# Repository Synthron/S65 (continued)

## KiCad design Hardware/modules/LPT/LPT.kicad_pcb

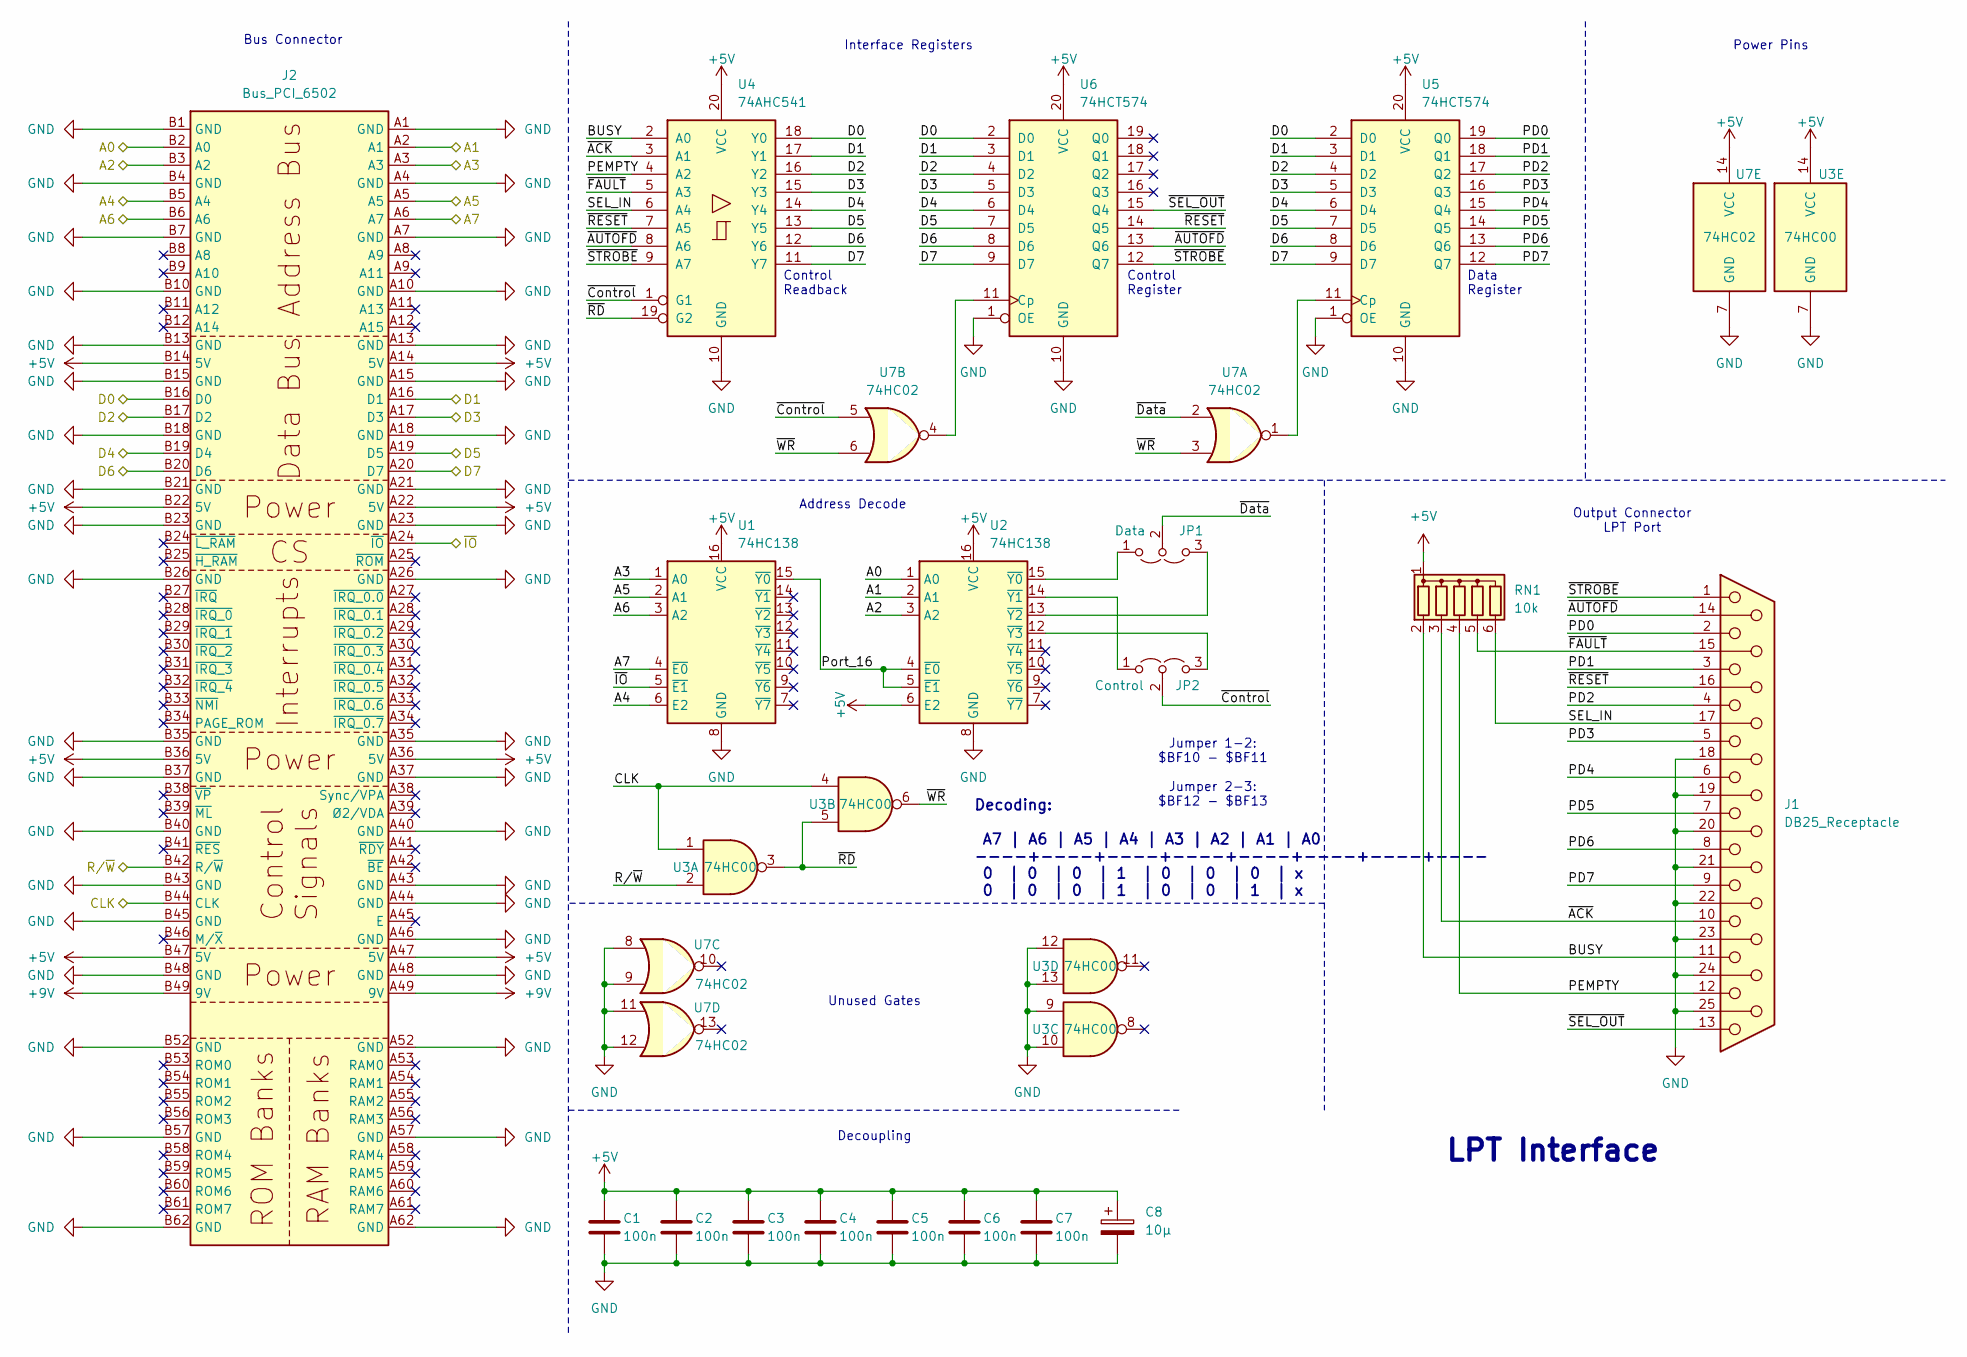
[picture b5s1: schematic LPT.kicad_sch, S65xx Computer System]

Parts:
C1, C2, C3, C4, C5, C6, C7: 100n; C_0805_2012Metric
C8: 10µ; CP_Radial_D5.0mm_P2.50mm
J1: DB25_Receptacle; DSUB-25_Female_EdgeMount_P2.77mm
J2: Bus_PCI_6502; BUS_PCI
JP1: Data; SolderJumper-3_P2.0mm_Open_TrianglePad1.0x1.5mm_NumberLabels
JP2: Control; SolderJumper-3_P2.0mm_Open_TrianglePad1.0x1.5mm_NumberLabels
RN1: 10k; R_Array_SIP6
U1, U2: 74HC138; DIP-16_W7.62mm
U3: 74HC00; DIP-14_W7.62mm
U4: 74AHC541; DIP-20_W7.62mm
U5, U6: 74HCT574; DIP-20_W7.62mm
U7: 74HC02; DIP-14_W7.62mm

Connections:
+5V: C1.1, C2.1, C3.1, C4.1, C5.1, C6.1, C7.1, C8.1, J2.A14 (5V), J2.A22 (5V), J2.A36 (5V), J2.A47 (5V), J2.B14 (5V), J2.B22 (5V), J2.B36 (5V), J2.B47 (5V), RN1.1 (common), U1.16 (VCC), U2.6 (E2), U2.16 (VCC), U3.14 (VCC), U4.20 (VCC), U5.20 (VCC), U6.20 (VCC), U7.14 (VCC)
+9V: J2.A49 (9V), J2.B49 (9V)
/A0: J2.B2 (A0), U2.1 (A0)
/A1: J2.A2 (A1), U2.2 (A1)
/A2: J2.B3 (A2), U2.3 (A2)
/A3: J2.A3, U1.1 (A0)
/A4: J2.B5 (A4), U1.6 (E2)
/A5: J2.A5, U1.2 (A1)
/A6: J2.B6 (A6), U1.3 (A2)
/A7: J2.A6 (A7), U1.4 (~E0)
/BUSY: J1.11, RN1.2 (R1), U4.2 (A0)
/CLK: J2.B44 (CLK), U3.1, U3.4
/D0: J2.B16 (D0), U4.18 (Y0), U5.2 (D0), U6.2 (D0)
/D1: J2.A16 (D1), U4.17 (Y1), U5.3 (D1), U6.3 (D1)
/D2: J2.B17 (D2), U4.16 (Y2), U5.4 (D2), U6.4 (D2)
/D3: J2.A17 (D3), U4.15 (Y3), U5.5 (D3), U6.5 (D3)
/D4: J2.B19 (D4), U4.14 (Y4), U5.6 (D4), U6.6 (D4)
/D5: J2.A19 (D5), U4.13 (Y5), U5.7 (D5), U6.7 (D5)
/D6: J2.B20 (D6), U4.12 (Y6), U5.8 (D6), U6.8 (D6)
/D7: J2.A20 (D7), U4.11 (Y7), U5.9 (D7), U6.9 (D7)
/PD0: J1.2, U5.19 (Q0)
/PD1: J1.3, U5.18 (Q1)
/PD2: J1.4, U5.17 (Q2)
/PD3: J1.5, U5.16 (Q3)
/PD4: J1.6, U5.15 (Q4)
/PD5: J1.7, U5.14 (Q5)
/PD6: J1.8, U5.13 (Q6)
/PD7: J1.9, U5.12 (Q7)
/PEMPTY: J1.12, RN1.4 (R3), U4.4 (A2)
/Port_16: U1.15 (~Y0), U2.4 (~E0), U2.5 (~E1)
/R/~W: J2.B42 (R/~W), U3.2
/SEL_IN: J1.17, RN1.6 (R5), U4.6 (A4)
/~ACK: J1.10, RN1.3 (R2), U4.3 (A1)
/~AUTOFD: J1.14, U4.8 (A6), U6.13 (Q6)
/~Control: JP2.2 (C), U4.1 (G1), U7.5
/~Data: JP1.2 (C), U7.2
/~FAULT: J1.15, RN1.5 (R4), U4.5 (A3)
/~IO: J2.A24 (~IO), U1.5 (~E1)
/~RD: U3.3, U3.5, U4.19 (G2)
/~RESET: J1.16, U4.7 (A5), U6.14 (Q5)
/~SEL_OUT: J1.13, U6.15 (Q4)
/~STROBE: J1.1, U4.9 (A7), U6.12 (Q7)
/~WR: U3.6, U7.3, U7.6
GND: C1.2, C2.2, C3.2, C4.2, C5.2, C6.2, C7.2, C8.2, J1.18, J1.19, J1.20, J1.21, J1.22, J1.23, J1.24, J1.25, J2.A1 (GND), J2.A4 (GND), J2.A7 (GND), J2.A10 (GND), J2.A13 (GND), J2.A15 (GND), J2.A18 (GND), J2.A21 (GND), J2.A23 (GND), J2.A26 (GND), J2.A35 (GND), J2.A37 (GND), J2.A40 (GND), J2.A43 (GND), J2.A44 (GND), J2.A46 (GND), J2.A48 (GND), J2.A52 (GND), J2.A57 (GND), J2.A62 (GND), J2.B1 (GND), J2.B4 (GND), J2.B7 (GND), J2.B10 (GND), J2.B13 (GND), J2.B15 (GND), J2.B18 (GND), J2.B21 (GND), J2.B23 (GND), J2.B26 (GND), J2.B35 (GND), J2.B37 (GND), J2.B40 (GND), J2.B43 (GND), J2.B45 (GND), J2.B48 (GND), J2.B52 (GND), J2.B57 (GND), J2.B62 (GND), U1.8 (GND), U2.8 (GND), U3.7 (GND), U3.9, U3.10, U3.12, U3.13, U4.10 (GND), U5.1 (OE), U5.10 (GND), U6.1 (OE), U6.10 (GND), U7.7 (GND), U7.8, U7.9, U7.11, U7.12
unnamed: JP1.1 (A), U2.15 (~Y0)
unnamed: JP1.3 (B), U2.13 (~Y2)
unnamed: JP2.1 (A), U2.14 (~Y1)
unnamed: JP2.3 (B), U2.12 (~Y3)
unnamed: U5.11 (Cp), U7.1
unnamed: U6.11 (Cp), U7.4

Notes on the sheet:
Interface Registers
Decoupling
Jumper 1-2: $BF10 - $BF11 Jumper 2-3: $BF12 - $BF13
Output Connector LPT Port
Decoding: A7 | A6 | A5 | A4 | A3 | A2 | A1 | A0 ----+----+----+----+----+----+----+---- 0 | 0 | 0 | 1 | 0 | 0 | 0 | x 0 | 0 | 0 | 1 | 0 | 0 | 1 | x
Power Pins
Address Decode
Control Register
Bus Connector
Unused Gates
Control Readback
Data Register
LPT Interface

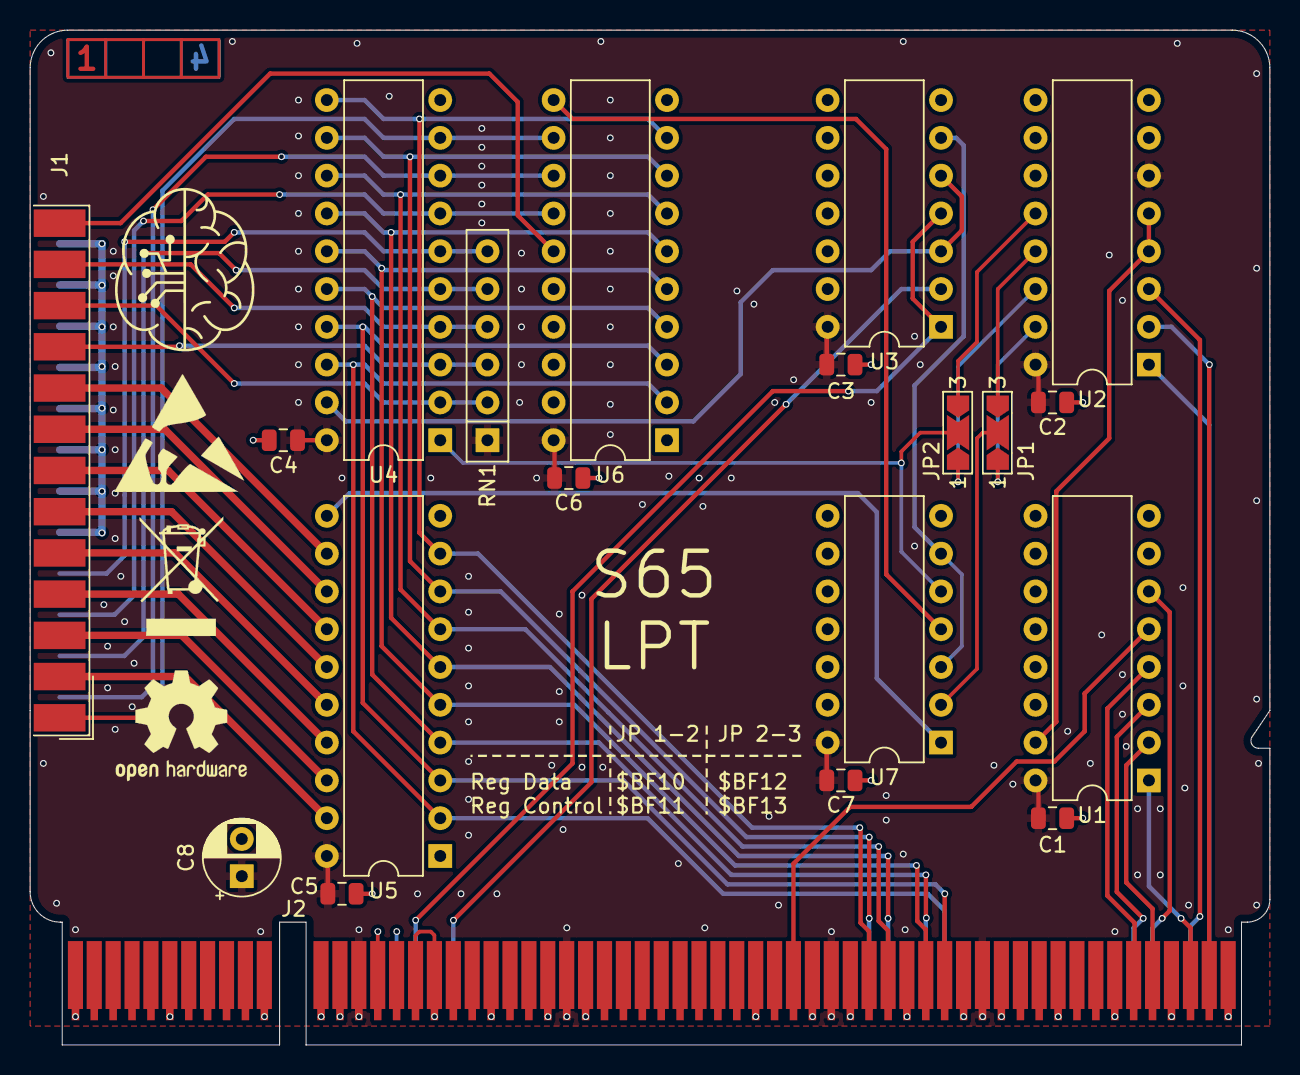
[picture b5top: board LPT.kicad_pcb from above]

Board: 4 copper layers, 83.3 x 68.2 mm, 21 parts (1 on the bottom side), 50 nets.

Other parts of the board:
Ref**: Val**; ladder_4

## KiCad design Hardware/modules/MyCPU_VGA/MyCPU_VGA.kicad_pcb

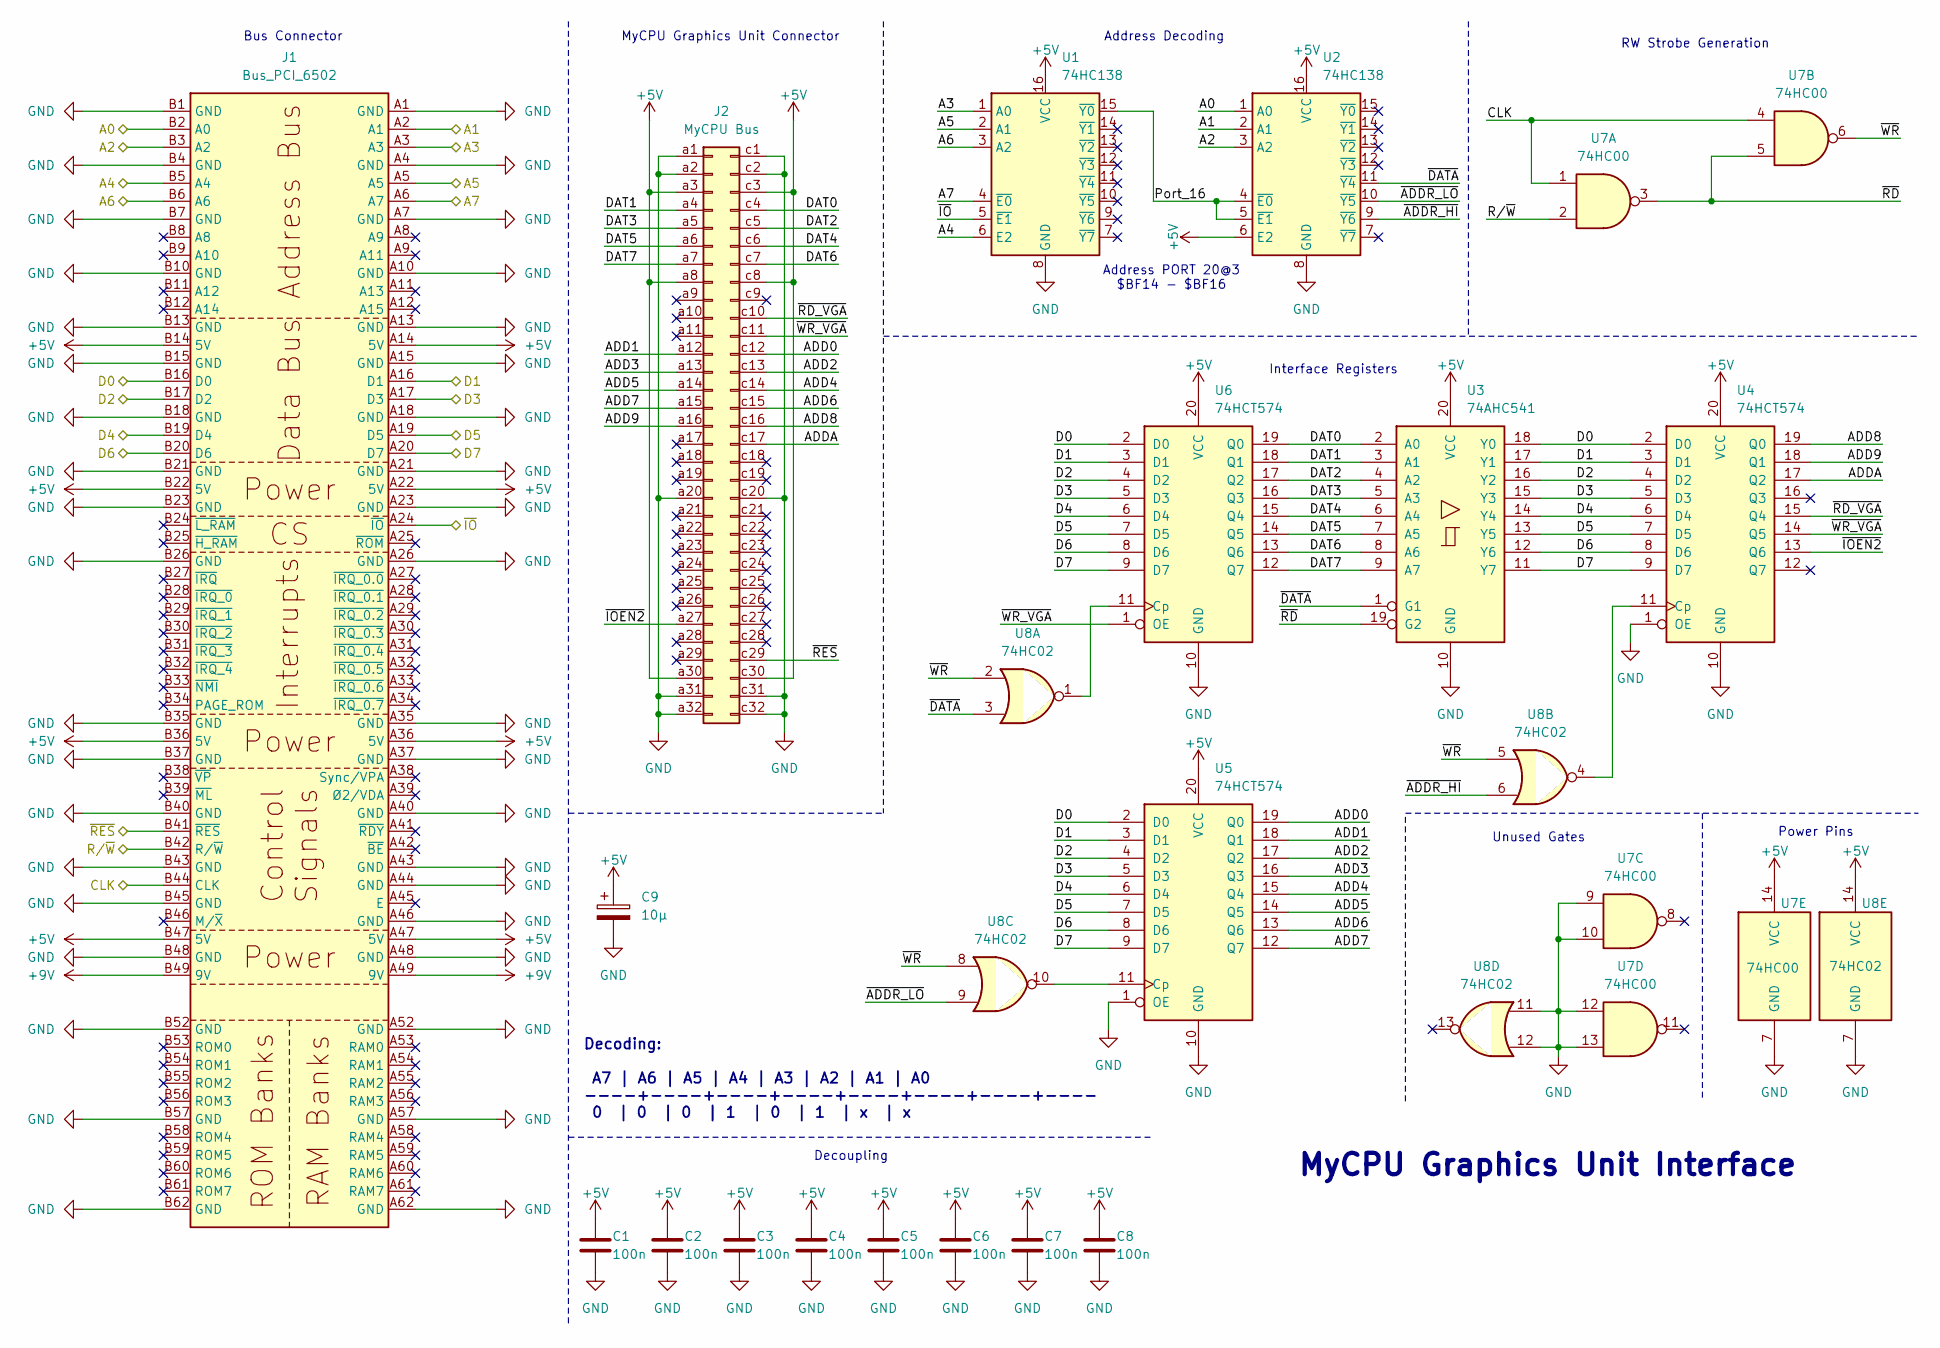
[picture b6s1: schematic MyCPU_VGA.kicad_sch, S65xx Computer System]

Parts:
C1, C2, C3, C4, C5, C6, C7, C8: 100n; C_0805_2012Metric
C9: 10µ; CP_Radial_D5.0mm_P2.50mm
J1: Bus_PCI_6502; BUS_PCI
J2: MyCPU Bus; DIN41612_C_2x32_Male_Horizontal_THT
U1, U2: 74HC138; DIP-16_W7.62mm
U3: 74AHC541; DIP-20_W7.62mm
U4, U5, U6: 74HCT574; DIP-20_W7.62mm
U7: 74HC00; DIP-14_W7.62mm
U8: 74HC02; DIP-14_W7.62mm

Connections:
+5V: C1.1, C2.1, C3.1, C4.1, C5.1, C6.1, C7.1, C8.1, C9.1, J1.A14 (5V), J1.A22 (5V), J1.A36 (5V), J1.A47 (5V), J1.B14 (5V), J1.B22 (5V), J1.B36 (5V), J1.B47 (5V), J2.a3, J2.a8, J2.a30, J2.c3, J2.c8, J2.c30, U1.16 (VCC), U2.6 (E2), U2.16 (VCC), U3.20 (VCC), U4.20 (VCC), U5.20 (VCC), U6.20 (VCC), U7.14 (VCC), U8.14 (VCC)
+9V: J1.A49 (9V), J1.B49 (9V)
/A0: J1.B2 (A0), U2.1 (A0)
/A1: J1.A2 (A1), U2.2 (A1)
/A2: J1.B3 (A2), U2.3 (A2)
/A3: J1.A3, U1.1 (A0)
/A4: J1.B5 (A4), U1.6 (E2)
/A5: J1.A5, U1.2 (A1)
/A6: J1.B6 (A6), U1.3 (A2)
/A7: J1.A6 (A7), U1.4 (~E0)
/ADD0: J2.c12, U5.19 (Q0)
/ADD1: J2.a12, U5.18 (Q1)
/ADD2: J2.c13, U5.17 (Q2)
/ADD3: J2.a13, U5.16 (Q3)
/ADD4: J2.c14, U5.15 (Q4)
/ADD5: J2.a14, U5.14 (Q5)
/ADD6: J2.c15, U5.13 (Q6)
/ADD7: J2.a15, U5.12 (Q7)
/ADD8: J2.c16, U4.19 (Q0)
/ADD9: J2.a16, U4.18 (Q1)
/ADDA: J2.c17, U4.17 (Q2)
/CLK: J1.B44 (CLK), U7.1, U7.4
/D0: J1.B16 (D0), U3.18 (Y0), U4.2 (D0), U5.2 (D0), U6.2 (D0)
/D1: J1.A16 (D1), U3.17 (Y1), U4.3 (D1), U5.3 (D1), U6.3 (D1)
/D2: J1.B17 (D2), U3.16 (Y2), U4.4 (D2), U5.4 (D2), U6.4 (D2)
/D3: J1.A17 (D3), U3.15 (Y3), U4.5 (D3), U5.5 (D3), U6.5 (D3)
/D4: J1.B19 (D4), U3.14 (Y4), U4.6 (D4), U5.6 (D4), U6.6 (D4)
/D5: J1.A19 (D5), U3.13 (Y5), U4.7 (D5), U5.7 (D5), U6.7 (D5)
/D6: J1.B20 (D6), U3.12 (Y6), U4.8 (D6), U5.8 (D6), U6.8 (D6)
/D7: J1.A20 (D7), U3.11 (Y7), U4.9 (D7), U5.9 (D7), U6.9 (D7)
/DAT0: J2.c4, U3.2 (A0), U6.19 (Q0)
/DAT1: J2.a4, U3.3 (A1), U6.18 (Q1)
/DAT2: J2.c5, U3.4 (A2), U6.17 (Q2)
/DAT3: J2.a5, U3.5 (A3), U6.16 (Q3)
/DAT4: J2.c6, U3.6 (A4), U6.15 (Q4)
/DAT5: J2.a6, U3.7 (A5), U6.14 (Q5)
/DAT6: J2.c7, U3.8 (A6), U6.13 (Q6)
/DAT7: J2.a7, U3.9 (A7), U6.12 (Q7)
/Port_16: U1.15 (~Y0), U2.4 (~E0), U2.5 (~E1)
/R/~W: J1.B42 (R/~W), U7.2
/~ADDR_HI: U2.9 (~Y6), U8.6
/~ADDR_LO: U2.10 (~Y5), U8.9
/~DATA: U2.11 (~Y4), U3.1 (G1), U8.3
/~IOEN2: J2.a27, U4.13 (Q6)
/~IO: J1.A24 (~IO), U1.5 (~E1)
/~RD_VGA: J2.c10, U4.15 (Q4)
/~RD: U3.19 (G2), U7.3, U7.5
/~RES: J1.B41 (~RES), J2.c29
/~WR_VGA: J2.c11, U4.14 (Q5), U6.1 (OE)
/~WR: U7.6, U8.2, U8.5, U8.8
GND: C1.2, C2.2, C3.2, C4.2, C5.2, C6.2, C7.2, C8.2, C9.2, J1.A1 (GND), J1.A4 (GND), J1.A7 (GND), J1.A10 (GND), J1.A13 (GND), J1.A15 (GND), J1.A18 (GND), J1.A21 (GND), J1.A23 (GND), J1.A26 (GND), J1.A35 (GND), J1.A37 (GND), J1.A40 (GND), J1.A43 (GND), J1.A44 (GND), J1.A46 (GND), J1.A48 (GND), J1.A52 (GND), J1.A57 (GND), J1.A62 (GND), J1.B1 (GND), J1.B4 (GND), J1.B7 (GND), J1.B10 (GND), J1.B13 (GND), J1.B15 (GND), J1.B18 (GND), J1.B21 (GND), J1.B23 (GND), J1.B26 (GND), J1.B35 (GND), J1.B37 (GND), J1.B40 (GND), J1.B43 (GND), J1.B45 (GND), J1.B48 (GND), J1.B52 (GND), J1.B57 (GND), J1.B62 (GND), J2.a1, J2.a2, J2.a20, J2.a31, J2.a32, J2.c1, J2.c2, J2.c20, J2.c31, J2.c32, U1.8 (GND), U2.8 (GND), U3.10 (GND), U4.1 (OE), U4.10 (GND), U5.1 (OE), U5.10 (GND), U6.10 (GND), U7.7 (GND), U7.9, U7.10, U7.12, U7.13, U8.7 (GND), U8.11, U8.12
unnamed: U4.11 (Cp), U8.4
unnamed: U5.11 (Cp), U8.10
unnamed: U6.11 (Cp), U8.1

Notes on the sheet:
Power Pins
MyCPU Graphics Unit Connector
RW Strobe Generation
Address Decoding
MyCPU Graphics Unit Interface
Interface Registers
Bus Connector
Unused Gates
Decoding: A7 | A6 | A5 | A4 | A3 | A2 | A1 | A0 ----+----+----+----+----+----+----+---- 0 | 0 | 0 | 1 | 0 | 1 | x | x
Address PORT 20@3 $BF14 - $BF16
Decoupling

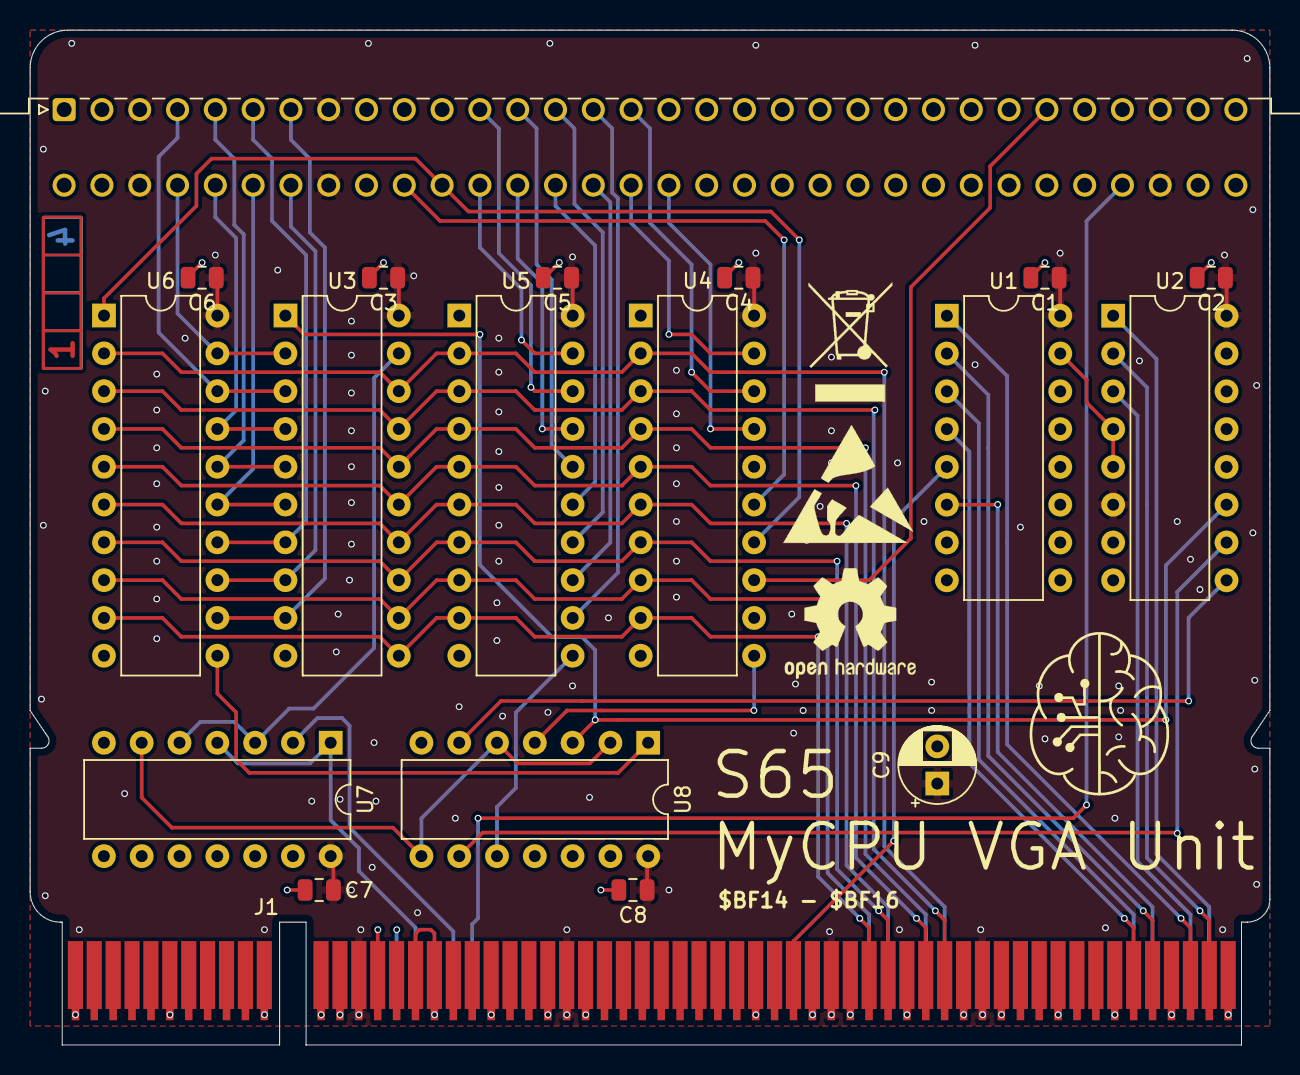
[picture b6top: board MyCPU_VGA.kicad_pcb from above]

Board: 4 copper layers, 83.3 x 68.2 mm, 20 parts (1 on the bottom side), 54 nets.

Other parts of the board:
Ref**: Val**; ladder_4

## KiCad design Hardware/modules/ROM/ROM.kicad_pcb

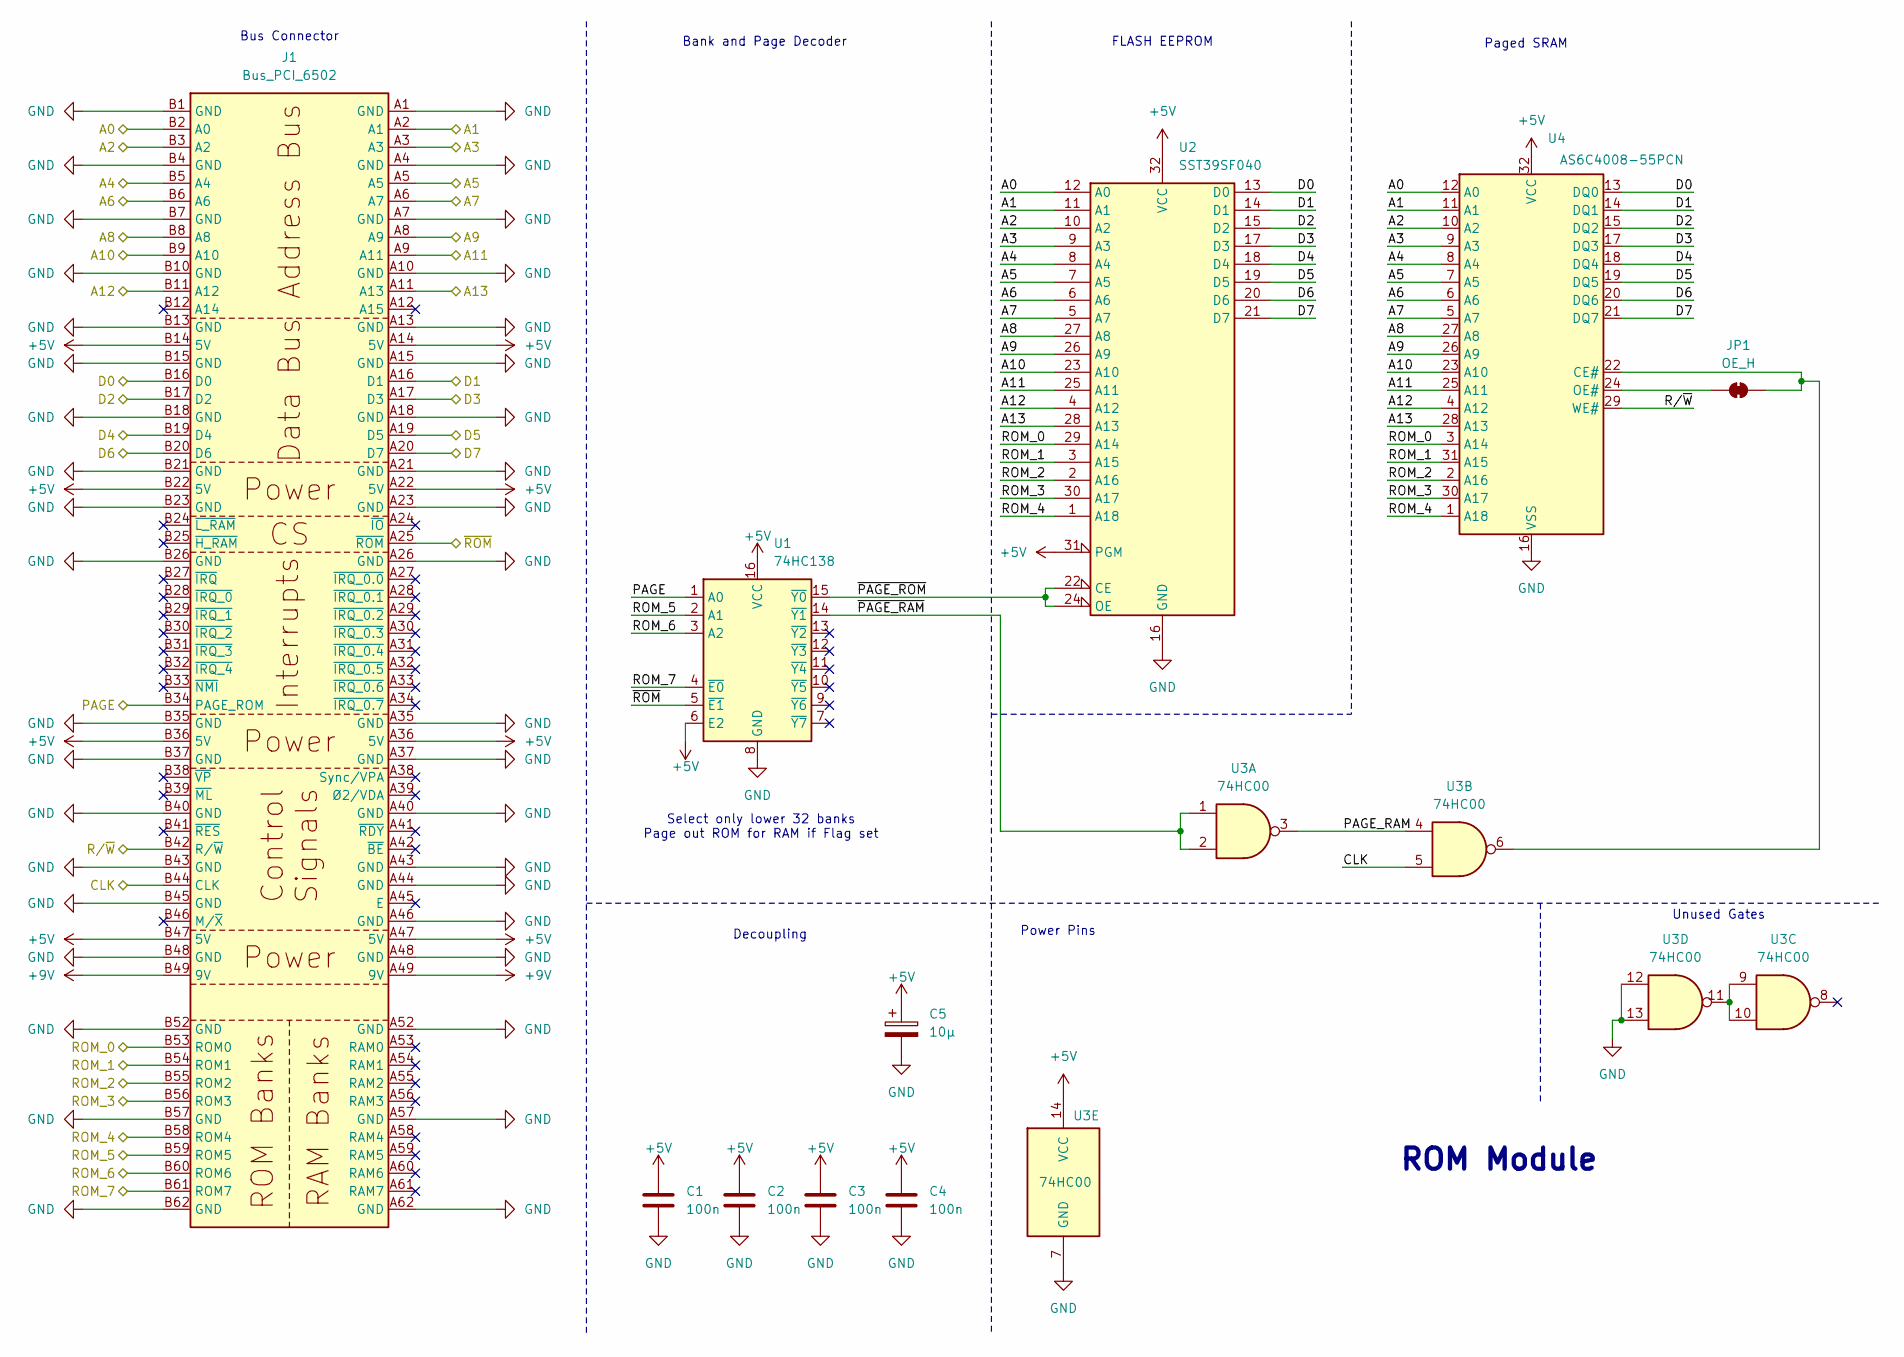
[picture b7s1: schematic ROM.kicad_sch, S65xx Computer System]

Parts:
C1, C2, C3, C4: 100n; C_0805_2012Metric
C5: 10µ; CP_Radial_D5.0mm_P2.50mm
J1: Bus_PCI_6502; BUS_PCI
JP1: OE_H; SolderJumper-2_P1.3mm_Bridged_RoundedPad1.0x1.5mm
U1: 74HC138; DIP-16_W7.62mm_LongPads
U2: SST39SF040; DIP-32_W15.24mm_LongPads
U3: 74HC00; DIP-14_W7.62mm_LongPads
U4: AS6C4008-55PCN; DIP-32_W15.24mm_LongPads

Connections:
+5V: C1.1, C2.1, C3.1, C4.1, C5.1, J1.A14 (5V), J1.A22 (5V), J1.A36 (5V), J1.A47 (5V), J1.B14 (5V), J1.B22 (5V), J1.B36 (5V), J1.B47 (5V), U1.6 (E2), U1.16 (VCC), U2.31 (PGM), U2.32 (VCC), U3.14 (VCC), U4.32 (VCC)
+9V: J1.A49 (9V), J1.B49 (9V)
/A0: J1.B2 (A0), U2.12 (A0), U4.12 (A0)
/A1: J1.A2 (A1), U2.11 (A1), U4.11 (A1)
/A2: J1.B3 (A2), U2.10 (A2), U4.10 (A2)
/A3: J1.A3, U2.9 (A3), U4.9 (A3)
/A4: J1.B5 (A4), U2.8 (A4), U4.8 (A4)
/A5: J1.A5, U2.7 (A5), U4.7 (A5)
/A6: J1.B6 (A6), U2.6 (A6), U4.6 (A6)
/A7: J1.A6 (A7), U2.5 (A7), U4.5 (A7)
/A8: J1.B8 (A8), U2.27 (A8), U4.27 (A8)
/A9: J1.A8 (A9), U2.26 (A9), U4.26 (A9)
/A10: J1.B9 (A10), U2.23 (A10), U4.23 (A10)
/A11: J1.A9 (A11), U2.25 (A11), U4.25 (A11)
/A12: J1.B11 (A12), U2.4 (A12), U4.4 (A12)
/A13: J1.A11 (A13), U2.28 (A13), U4.28 (A13)
/CLK: J1.B44 (CLK), U3.5
/D0: J1.B16 (D0), U2.13 (D0), U4.13 (DQ0)
/D1: J1.A16 (D1), U2.14 (D1), U4.14 (DQ1)
/D2: J1.B17 (D2), U2.15 (D2), U4.15 (DQ2)
/D3: J1.A17 (D3), U2.17 (D3), U4.17 (DQ3)
/D4: J1.B19 (D4), U2.18 (D4), U4.18 (DQ4)
/D5: J1.A19 (D5), U2.19 (D5), U4.19 (DQ5)
/D6: J1.B20 (D6), U2.20 (D6), U4.20 (DQ6)
/D7: J1.A20 (D7), U2.21 (D7), U4.21 (DQ7)
/PAGE: J1.B34 (PAGE_ROM), U1.1 (A0)
/PAGE_RAM: U3.3, U3.4
/ROM_0: J1.B53 (ROM0), U2.29 (A14), U4.3 (A14)
/ROM_1: J1.B54 (ROM1), U2.3 (A15), U4.31 (A15)
/ROM_2: J1.B55 (ROM2), U2.2 (A16), U4.2 (A16)
/ROM_3: J1.B56 (ROM3), U2.30 (A17), U4.30 (A17)
/ROM_4: J1.B58 (ROM4), U2.1 (A18), U4.1 (A18)
/ROM_5: J1.B59 (ROM5), U1.2 (A1)
/ROM_6: J1.B60 (ROM6), U1.3 (A2)
/ROM_7: J1.B61 (ROM7), U1.4 (~E0)
/R/~W: J1.B42 (R/~W), U4.29 (WE#)
/~PAGE_RAM: U1.14 (~Y1), U3.1, U3.2
/~PAGE_ROM: U1.15 (~Y0), U2.22 (CE), U2.24 (OE)
/~ROM: J1.A25 (~ROM), U1.5 (~E1)
GND: C1.2, C2.2, C3.2, C4.2, C5.2, J1.A1 (GND), J1.A4 (GND), J1.A7 (GND), J1.A10 (GND), J1.A13 (GND), J1.A15 (GND), J1.A18 (GND), J1.A21 (GND), J1.A23 (GND), J1.A26 (GND), J1.A35 (GND), J1.A37 (GND), J1.A40 (GND), J1.A43 (GND), J1.A44 (GND), J1.A46 (GND), J1.A48 (GND), J1.A52 (GND), J1.A57 (GND), J1.A62 (GND), J1.B1 (GND), J1.B4 (GND), J1.B7 (GND), J1.B10 (GND), J1.B13 (GND), J1.B15 (GND), J1.B18 (GND), J1.B21 (GND), J1.B23 (GND), J1.B26 (GND), J1.B35 (GND), J1.B37 (GND), J1.B40 (GND), J1.B43 (GND), J1.B45 (GND), J1.B48 (GND), J1.B52 (GND), J1.B57 (GND), J1.B62 (GND), U1.8 (GND), U2.16 (GND), U3.7 (GND), U3.12, U3.13, U4.16 (VSS)
unnamed: JP1.1 (A), U4.24 (OE#)
unnamed: JP1.2 (B), U3.6, U4.22 (CE#)
unnamed: U3.9, U3.10, U3.11

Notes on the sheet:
Paged SRAM
Bank and Page Decoder
Select only lower 32 banks Page out ROM for RAM if Flag set
Bus Connector
FLASH EEPROM
Decoupling
Unused Gates
Power Pins
ROM Module

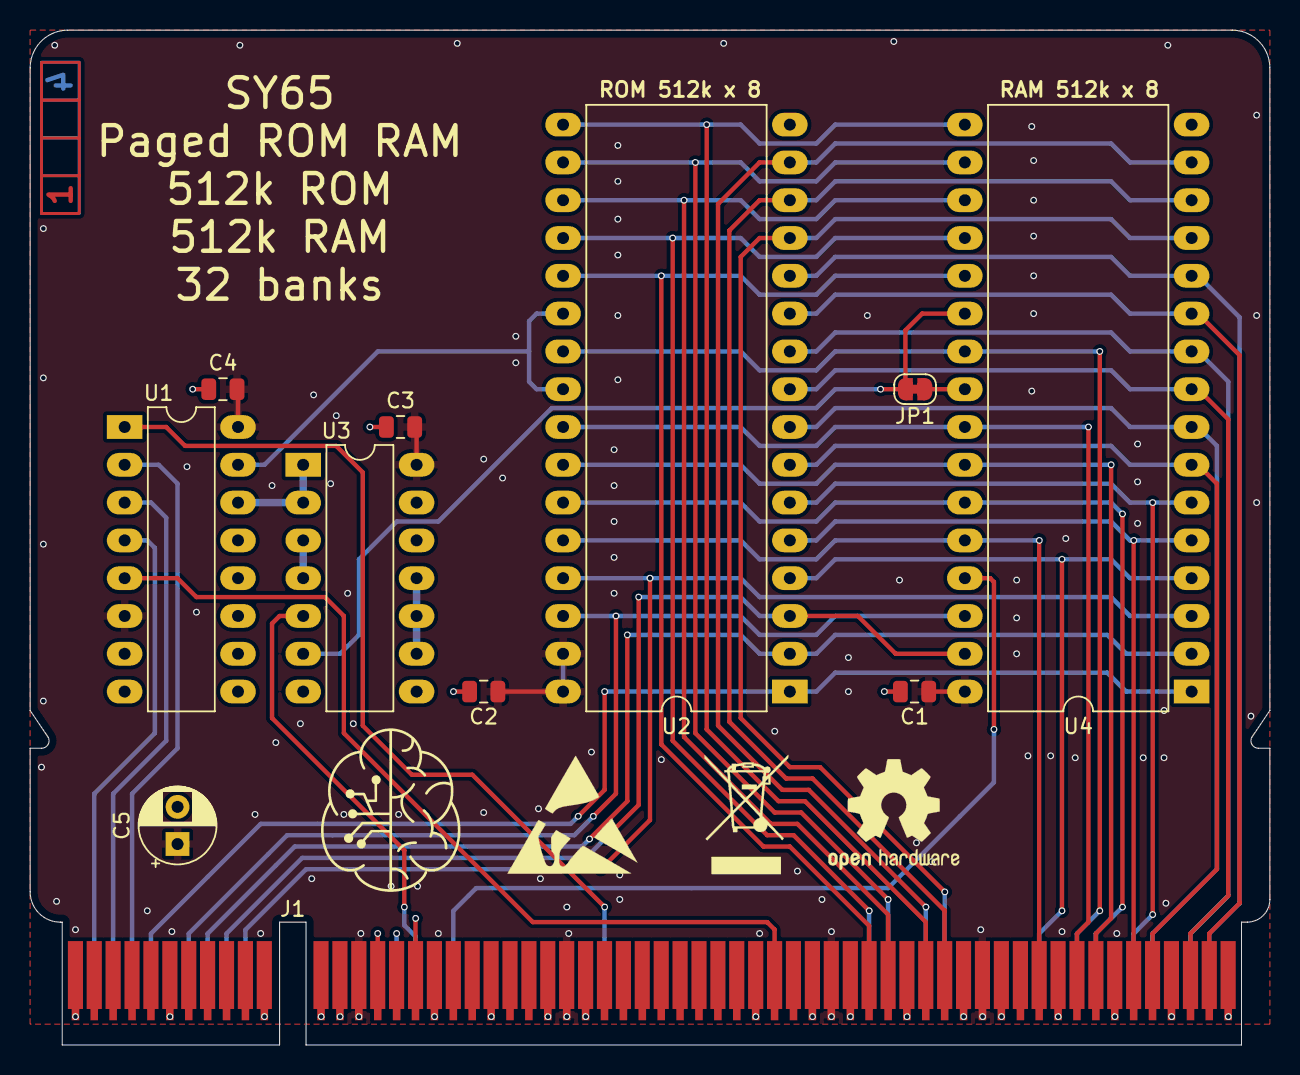
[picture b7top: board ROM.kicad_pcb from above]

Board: 4 copper layers, 83.3 x 68.2 mm, 12 parts (1 on the bottom side), 43 nets.

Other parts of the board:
Ref**: Val**; ladder_4
